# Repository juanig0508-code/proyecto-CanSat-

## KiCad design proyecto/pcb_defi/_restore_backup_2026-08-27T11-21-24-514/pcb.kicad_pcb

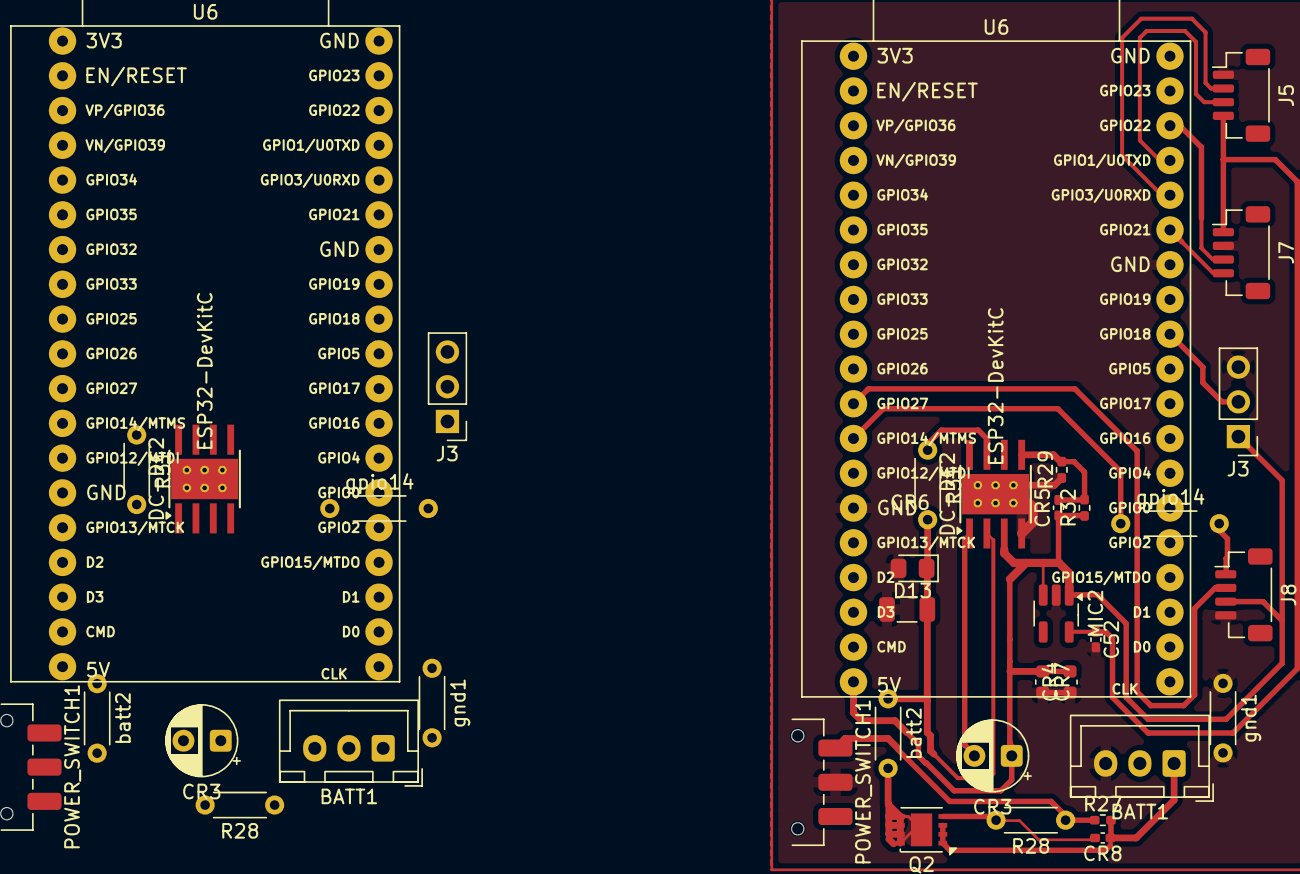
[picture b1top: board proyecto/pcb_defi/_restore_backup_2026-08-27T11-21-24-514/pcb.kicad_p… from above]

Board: 2 copper layers, 37 parts (0 on the bottom side), 19 nets.

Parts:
BATT1, BATT1#2: Conn_01x03_Pin; JST_XH_B3B-XH-A_1x03_P2.50mm_Vertical
C52: 10uF; C_0402_1005Metric_Pad0.74x0.62mm_HandSolder
CR3, CR3#2: 0.1uF; CP_Radial_D5.0mm_P2.50mm
CR4, CR7: 0.1uF; C_0603_1608Metric
CR5: 0.1uF; C_0402_1005Metric_Pad0.74x0.62mm_HandSolder
CR6: 47uF; C_1206_3216Metric
CR8: 1uF; C_0402_1005Metric_Pad0.74x0.62mm_HandSolder
D13: D; D_0805_2012Metric_Pad1.15x1.40mm_HandSolder
DC-DC2, DC-DC2#2: Texas_HTSOP-8-1EP_3.9x4.9mm_P1.27mm_EP2.95x4.9mm_Mask2.4x3.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
J3, J3#2: Conn_01x03_Pin; PinHeader_1x03_P2.54mm_Vertical
J5, J8: pines de gps; JST_SH_BM04B-SRSS-TB_1x04-1MP_P1.00mm_Vertical
J7: pines de senspores; JST_SH_BM04B-SRSS-TB_1x04-1MP_P1.00mm_Vertical
MIC2: SOT-23-5_HandSoldering
POWER_SWITCH1, POWER_SWITCH1#2: SW_DPDT_x2; SW_SPDT_CK_JS102011SAQN
Q2: AON7423; DFN-8-1EP_3x3mm_P0.65mm_EP1.55x2.4mm
R27: 10K; R_0402_1005Metric_Pad0.72x0.64mm_HandSolder
R28, R28#2: 1K; R_Axial_DIN0204_L3.6mm_D1.6mm_P5.08mm_Horizontal
R29: 45K; R_0402_1005Metric_Pad0.72x0.64mm_HandSolder
R31, R31#2: 100k; R_Axial_DIN0204_L3.6mm_D1.6mm_P5.08mm_Horizontal
R32: 60k; R_0402_1005Metric_Pad0.72x0.64mm_HandSolder
U6, U6#2: ESP32-DevKitC
batt2, batt2#2: batt; R_Axial_DIN0204_L3.6mm_D1.6mm_P5.08mm_Horizontal
gnd1, gnd1#2: gnd; R_Axial_DIN0204_L3.6mm_D1.6mm_P5.08mm_Horizontal
gpio14, gpio14#2: gpio14; R_Axial_DIN0204_L3.6mm_D1.6mm_P5.08mm_Horizontal

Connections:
+3V3: C52.1, J5.4, J7.1, MIC2.5 (VOUT)
+5V: CR3.1, CR3#2.1, CR4.2, CR5.1, CR7.1, DC-DC2.3 (SW), DC-DC2#2.3 (SW), J3.1, J3#2.1, J8.3, MIC2.1 (VIN), MIC2.3 (CE), R32.1, U6.19 (5V), U6#2.19 (5V)
/BATT: CR6.2, D13.1 (K), DC-DC2.2 (VIN), DC-DC2#2.2 (VIN), R31.2, R31#2.2, batt2.1, batt2#2.1
/LIPO+: BATT1.1, BATT1#2.1, CR8.1, Q2.3 (S), R27.2
GND: BATT1.3, BATT1#2.3, C52.2, CR4.1, CR6.1, CR7.2, D13.2 (A), DC-DC2.4 (GND), DC-DC2.9 (EPAD), DC-DC2#2.4 (GND), DC-DC2#2.9 (EPAD), J3.3, J3#2.3, J5.1, J7.2, J8.4, MIC2.2 (VSS), POWER_SWITCH1.2 (B), POWER_SWITCH1#2.2 (B), R29.1, U6.14 (GND), U6.32 (GND), U6.38 (GND), U6#2.14 (GND), U6#2.32 (GND), U6#2.38 (GND), gnd1.1, gnd1.2, gnd1#2.1, gnd1#2.2
unnamed: CR3.2, CR3#2.2, DC-DC2.1 (BST), DC-DC2#2.1 (BST)
unnamed: DC-DC2.7 (EN), DC-DC2#2.7 (EN), R31.1, R31#2.1
unnamed: CR5.2, DC-DC2.5 (FB), DC-DC2#2.5 (FB), R29.2, R32.2
unnamed: J3.2, J3#2.2, U6.30 (GPIO18), U6#2.30 (GPIO18)
unnamed: J5.2, U6.34 (U0RXD/GPIO3), U6#2.34 (U0RXD/GPIO3)
unnamed: J5.3, U6.35 (U0TXD/GPIO1), U6#2.35 (U0TXD/GPIO1)
unnamed: J7.3, U6.36 (GPIO22), U6#2.36 (GPIO22)
unnamed: J7.4, U6.33 (GPIO21), U6#2.33 (GPIO21)
unnamed: J8.1, gpio14.2, gpio14#2.2
unnamed: J8.2, U6.11 (ADC2_CH7/GPIO27), U6#2.11 (ADC2_CH7/GPIO27)
unnamed: POWER_SWITCH1.1 (A), POWER_SWITCH1#2.1 (A), R27.1, R28.1, R28#2.1
unnamed: Q2.1 (D), batt2.2, batt2#2.2
unnamed: CR8.2, Q2.2 (G), R28.2, R28#2.2
unnamed: U6.12 (MTMS/GPIO14/ADC2_CH6), U6#2.12 (MTMS/GPIO14/ADC2_CH6), gpio14.1, gpio14#2.1

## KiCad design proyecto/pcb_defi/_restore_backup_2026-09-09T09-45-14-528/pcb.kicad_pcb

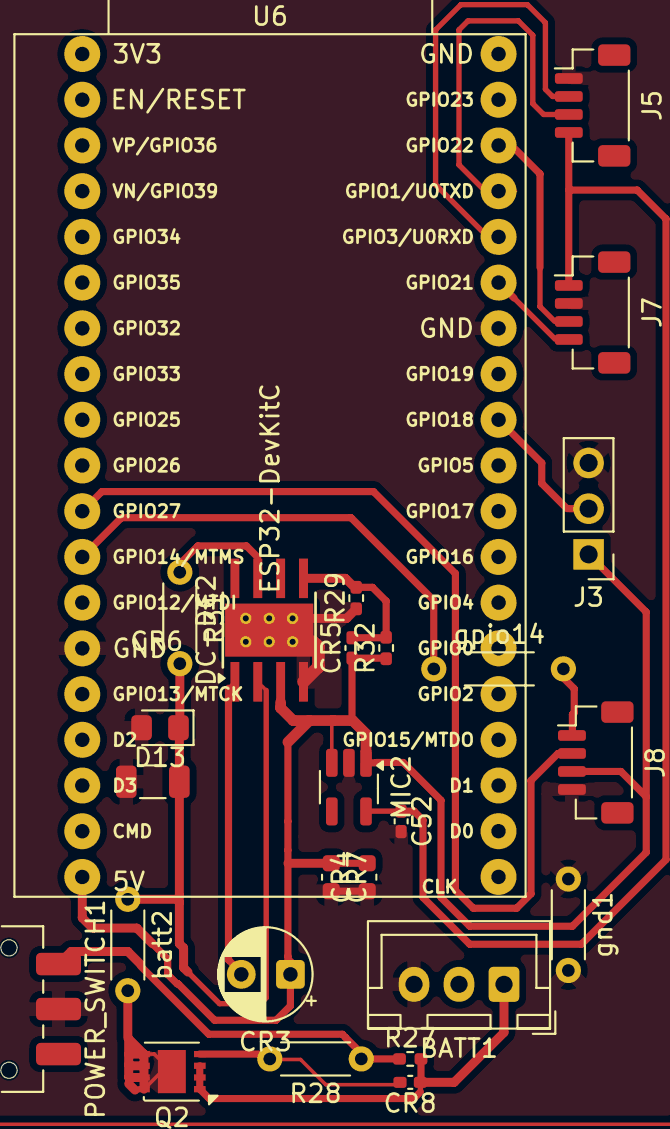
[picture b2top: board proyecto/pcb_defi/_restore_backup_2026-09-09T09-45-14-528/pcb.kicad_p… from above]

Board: 2 copper layers, 26 parts (0 on the bottom side), 19 nets.

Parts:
BATT1: Conn_01x03_Pin; JST_XH_B3B-XH-A_1x03_P2.50mm_Vertical
C52: 10uF; C_0402_1005Metric_Pad0.74x0.62mm_HandSolder
CR3: 0.1uF; CP_Radial_D5.0mm_P2.50mm
CR4, CR7: 0.1uF; C_0603_1608Metric
CR5: 0.1uF; C_0402_1005Metric_Pad0.74x0.62mm_HandSolder
CR6: 47uF; C_1206_3216Metric
CR8: 1uF; C_0402_1005Metric_Pad0.74x0.62mm_HandSolder
D13: D; D_0805_2012Metric_Pad1.15x1.40mm_HandSolder
DC-DC2: Texas_HTSOP-8-1EP_3.9x4.9mm_P1.27mm_EP2.95x4.9mm_Mask2.4x3.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
J3: Conn_01x03_Pin; PinHeader_1x03_P2.54mm_Vertical
J5, J8: pines de gps; JST_SH_BM04B-SRSS-TB_1x04-1MP_P1.00mm_Vertical
J7: pines de senspores; JST_SH_BM04B-SRSS-TB_1x04-1MP_P1.00mm_Vertical
MIC2: SOT-23-5_HandSoldering
POWER_SWITCH1: SW_DPDT_x2; SW_SPDT_CK_JS102011SAQN
Q2: AON7423; DFN-8-1EP_3x3mm_P0.65mm_EP1.55x2.4mm
R27: 10K; R_0402_1005Metric_Pad0.72x0.64mm_HandSolder
R28: 1K; R_Axial_DIN0204_L3.6mm_D1.6mm_P5.08mm_Horizontal
R29: 45K; R_0402_1005Metric_Pad0.72x0.64mm_HandSolder
R31: 100k; R_Axial_DIN0204_L3.6mm_D1.6mm_P5.08mm_Horizontal
R32: 60k; R_0402_1005Metric_Pad0.72x0.64mm_HandSolder
U6: ESP32-DevKitC
batt2: batt; R_Axial_DIN0204_L3.6mm_D1.6mm_P5.08mm_Horizontal
gnd1: gnd; R_Axial_DIN0204_L3.6mm_D1.6mm_P5.08mm_Horizontal
gpio14: gpio14; R_Axial_DIN0204_L3.6mm_D1.6mm_P5.08mm_Horizontal

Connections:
+3V3: C52.1, J5.4, J7.1, MIC2.5 (VOUT)
+5V: CR3.1, CR4.2, CR5.1, CR7.1, DC-DC2.3 (SW), J3.1, J8.3, MIC2.1 (VIN), MIC2.3 (CE), R32.1, U6.19 (5V)
/BATT: CR6.2, D13.1 (K), DC-DC2.2 (VIN), R31.2, batt2.1
/LIPO+: BATT1.1, CR8.1, Q2.3 (S), R27.2
GND: BATT1.3, C52.2, CR4.1, CR6.1, CR7.2, D13.2 (A), DC-DC2.4 (GND), DC-DC2.9 (EPAD), J3.3, J5.1, J7.2, J8.4, MIC2.2 (VSS), POWER_SWITCH1.2 (B), R29.1, U6.14 (GND), U6.32 (GND), U6.38 (GND), gnd1.1, gnd1.2
unnamed: CR3.2, DC-DC2.1 (BST)
unnamed: DC-DC2.7 (EN), R31.1
unnamed: CR5.2, DC-DC2.5 (FB), R29.2, R32.2
unnamed: J3.2, U6.30 (GPIO18)
unnamed: J5.2, U6.34 (U0RXD/GPIO3)
unnamed: J5.3, U6.35 (U0TXD/GPIO1)
unnamed: J7.3, U6.36 (GPIO22)
unnamed: J7.4, U6.33 (GPIO21)
unnamed: J8.1, gpio14.2
unnamed: J8.2, U6.11 (ADC2_CH7/GPIO27)
unnamed: POWER_SWITCH1.1 (A), R27.1, R28.1
unnamed: Q2.1 (D), batt2.2
unnamed: CR8.2, Q2.2 (G), R28.2
unnamed: U6.12 (MTMS/GPIO14/ADC2_CH6), gpio14.1
